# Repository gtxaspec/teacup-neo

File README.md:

# Teacup Neo

T41 (QFN96) adaptation of the [Teacup Rev-C](https://github.com/CapnRon/Teacup) T31 development board.

Targets **T41NQ (128MB)**, **T41XQ (256MB)**, and **T41LQ (64MB)** — all three are
pin-identical in the QFN96 package, so one layout serves all three as a stuffing
option (LQ needs the DDR rail set to 1.8V instead of 1.35V via the FB divider).

> **Where this is going:** teacup-neo is the single-SoC (T41) proof for a modular
> platform — a universal baseboard + per-SoC interposer modules on a **DDR4 card-edge
> socket** (UDIMM-288 desktop primary) that host any Ingenic T-series/A1 SoC
> regardless of package. Full spec in [`docs/UNIVERSAL.md`](docs/UNIVERSAL.md).

## Status

| Stage | State |
|-------|-------|
| Pin map / power design | complete, verified against 3 datasheets |
| QFN96 footprint + T41NQ symbol | KiCad-validated |
| Schematic | **netlist-verified** — all 97 SoC pins on intended nets, 0 peripheral connections lost |
| PCB netlist applied | 479 pads re-netted, 0 mismatch |
| Routing | **~83% auto-routed** (FreeRouting); 78 nets + placement + 3 shorts need GUI finishing |
| Manufacturing outputs | BOM/pos complete; Gerbers are a **draft** (board not yet fab-ready) |

**This board is NOT fab-ready.** The design (schematic + netlist) is complete and
fully verified, but the PCB was auto-routed headlessly with best-effort blind
placement. Before fabrication it needs, in the KiCad GUI:
- placement de-overlap of the bottom-side power section (7 courtyard overlaps)
- the 78 remaining ratsnest connections routed
- 3 shorts / clearance violations resolved
- **MIPI CSI routed as 100 ohm impedance-controlled differential pairs** (an
  autorouter does not do controlled impedance)
- SFC/DDR length + return-path review per the T41 Hardware Design Guide

## Power tree

2x SY8089A1AAC buck (core 0.8V/2A EN<-1.35V, DDR 1.35V EN<-1.8V) + kept AZ1117
LDOs (3.3V, 1.8V). EN cascade gives the datasheet power-on order. See `docs/POWER.md`.

## Layout

- `hw/` — KiCad project (based on TeaCup(C)3.3)
- `hw/Manufacturing/` — draft Gerbers, drill, BOM, position, DRC report
- `docs/` — pin maps, power design, netlist verification
- `scripts/` — the headless generators (footprint, symbol, schematic, PCB, routing)
- `reference/` — upstream 3.3 artifacts

Built headlessly with KiCad 9.0.2 (kicad-cli + pcbnew) + FreeRouting 1.9.0.

License: GPL-3.0 (inherited from upstream).

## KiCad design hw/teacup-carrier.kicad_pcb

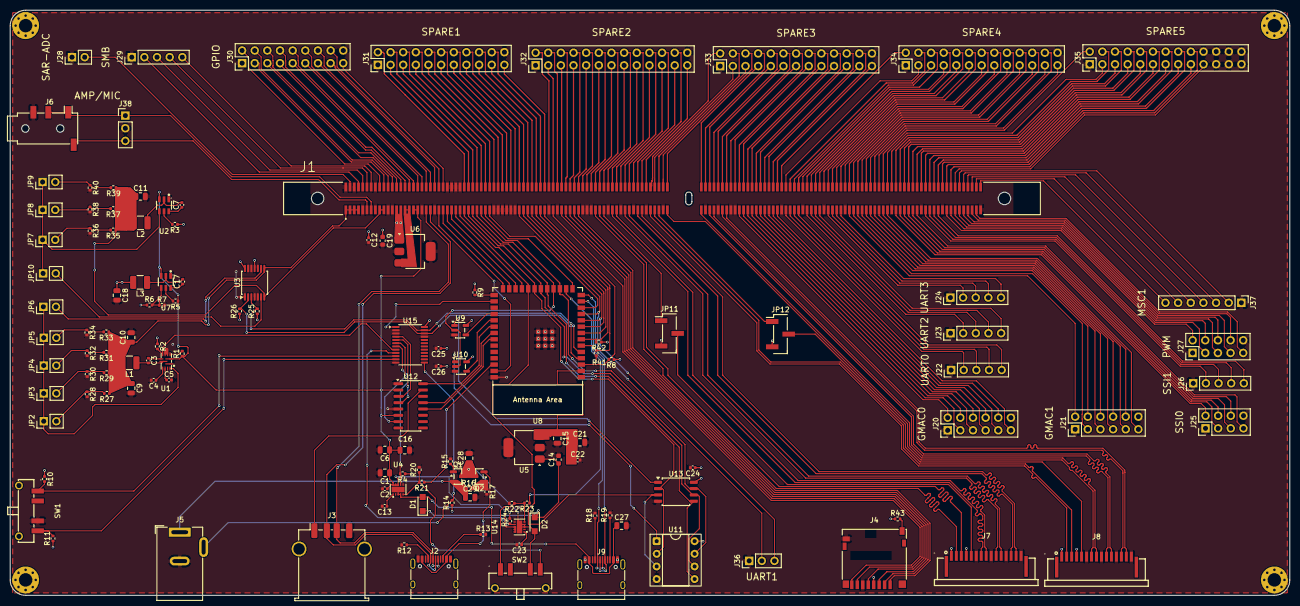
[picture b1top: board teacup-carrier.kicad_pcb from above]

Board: 4 copper layers, 257.0 x 117.5 mm, 137 parts (0 on the bottom side), 308 nets.

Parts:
C1, C9, C10, C11, C18: 22uF; C_0805_2012Metric
C2, C3, C7, C12, C17, C22, C24, C25, C26: 100nF; C_0402_1005Metric
C4: 1uF; C_0402_1005Metric
C5: 4.7nF; C_0402_1005Metric
C6, C15, C16, C21, C27, C28, C29: 10uF; C_0805_2012Metric
C13, C23: 1nF; C_0402_1005Metric
C14, C19: 1uF; C_0603_1608Metric
D1, D2: PMEG2010ER; Nexperia_CFP3_SOD-123W
H1, H2, H3, H4: MountingHole_Pad; MountingHole_2.7mm_M2.5_Pad_Via
J1: AH58893-T9B10-3F; DDR4288S0511H_UDIMM288
J2, J9: TYPE-C-31-M-12; USB_C_Receptacle_HRO_TYPE-C-31-M-12
J3: TE_292303-7; USB_A_TE_292303-7_Horizontal
J4: Hirose_DM3D-SF; microSD_HC_Hirose_DM3D-SF
J5: Wuerth_694106301002; BarrelJack_Wuerth_6941xx301002
J6: AudioJack4_Ground; Jack_3.5mm_PJ320D_Horizontal
J7, J8: SFW15R-2STE1LF; FPC-SMD_15P-P1.00_SFW15R-2STE1LF
J20: HDR_J20; PinHeader_2x06_P2.54mm_Vertical
J21: HDR_J21; PinHeader_2x06_P2.54mm_Vertical
J22: HDR_J22; PinHeader_1x05_P2.54mm_Vertical
J23: HDR_J23; PinHeader_1x05_P2.54mm_Vertical
J24: HDR_J24; PinHeader_1x05_P2.54mm_Vertical
J25: HDR_J25; PinHeader_2x04_P2.54mm_Vertical
J26: HDR_J26; PinHeader_1x05_P2.54mm_Vertical
J27: HDR_J27; PinHeader_2x05_P2.54mm_Vertical
J28: HDR_J28; PinHeader_1x02_P2.54mm_Vertical
J29: HDR_J29; PinHeader_1x05_P2.54mm_Vertical
J30: HDR_J30; PinHeader_2x09_P2.54mm_Vertical
J31: HDR_J31; PinHeader_2x11_P2.54mm_Vertical
J32: HDR_J32; PinHeader_2x13_P2.54mm_Vertical
J33: HDR_J33; PinHeader_2x13_P2.54mm_Vertical
J34: HDR_J34; PinHeader_2x13_P2.54mm_Vertical
J35: HDR_J35; PinHeader_2x13_P2.54mm_Vertical
J36: HDR_J36; PinHeader_1x03_P2.54mm_Vertical
J37: HDR_J37; PinHeader_1x07_P2.54mm_Vertical
J38: AMP_MIC_TAP; PinHeader_1x03_P2.54mm_Vertical
JP2: 0.8V; PinHeader_1x02_P2.54mm_Vertical
JP3: 0.9V; PinHeader_1x02_P2.54mm_Vertical
JP4: 1.0V; PinHeader_1x02_P2.54mm_Vertical
JP5: 1.1V; PinHeader_1x02_P2.54mm_Vertical
JP6, JP10: COMPUTER; PinHeader_1x02_P2.54mm_Vertical
JP7: 1.35V; PinHeader_1x02_P2.54mm_Vertical
JP8: 1.5V; PinHeader_1x02_P2.54mm_Vertical
JP9: 1.8V; PinHeader_1x02_P2.54mm_Vertical
JP11, JP12: EN_SEL; PinHeader_1x03_P2.54mm_Vertical_SMD_Pin1Left
L1, L2, L3: 2.2uH; L_1210_3225Metric
Q1, Q2: AO3401A; SOT-23
R1, R3, R5, R15, R17, R20, R22: 100k; R_0402_1005Metric
R2, R4, R7, R8, R9, R10, R11, R14, R24: 10k; R_0402_1005Metric
R6: 31.6k; R_0402_1005Metric
R12, R13, R18, R19: 5.1k; R_0402_1005Metric
R16, R25, R26, R41, R42: 4.7k; R_0402_1005Metric
R21, R23: 1k; R_0402_1005Metric
R27: 3.32k; R_0402_1005Metric
R28, R30, R32, R34, R36, R38, R40: 10.0k; R_0402_1005Metric
R29: 4.99k; R_0402_1005Metric
R31: 6.65k; R_0402_1005Metric
R33: 8.25k; R_0402_1005Metric
R35: 6.81k; R_0402_1005Metric
R37: 8.66k; R_0402_1005Metric
R39: 12.4k; R_0402_1005Metric
R43: 1M; R_0402_1005Metric
SW1, SW2: SSSS711403; SW-TH_SSSS711403
U1: AP62600SJ-7; QFN-12_L3.0-W2.0-P0.50-TL_AP62600SJ-7
U2, U7: AP62300WU-7; TSOT-23-6_L2.9-W1.6-P0.95-LS2.8-BL
U3: MCP4661-104E_ST; TSSOP-14_4.4x5mm_P0.65mm
U4, U14: TPS22990DMLR; WSON-10_L3.0-W2.0-P0.50-BL-EP_TI_DML
U5: AZ1117CH-3.3TRG1; SOT-223-3_TabPin2
U6: AZ1117CH-1.8TRG1; SOT-223-3_TabPin2
U8: ESP32-S3-WROOM-1-N16R2; ESP32-S3-WROOM-1
U9, U10: TS5A3166; SOT-23-5
U11: DIP-8 Socket; DIP-8_W7.62mm_Socket
U12: TPS2053BDR; SOIC-16_3.9x9.9mm_P1.27mm
U13: W25Q32JVSS; SOIC-8_5.3x5.3mm_P1.27mm
U15: TCA9555PWR; TSSOP-24_4.4x7.8mm_P0.65mm

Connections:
+1V8: J1.15, J1.16, U6.3 (OUT)
+3V3: C12.1, C18.1, C19.1, C24.1, C25.1, C26.1, J1.13, J1.14, J4.4 (VDD), J7.1, J7.4, J8.1, J8.4, JP11.3, JP12.3, L3.2, R2.1, R3.1, R4.1, R6.1, R8.1, R9.1, R10.1, R11.1, R14.1, R24.1, R25.1, R26.1, R41.1, R42.1, R43.1, U3.11 (WP), U3.14 (VDD), U6.1 (IN), U9.5 (V+), U10.5 (V+), U11.8 (VCC), U13.8 (VCC), U15.24 (VCC)
+3V3_ALWAYS: C15.1, C21.1, C22.1, U5.3 (OUT), U8.2 (3V3)
+5V_ALT: C28.1, D2.2 (A), Q1.3 (D), Q2.3 (D), SW2.3, U14.3 (VIN), U14.4 (VBIAS), U14.11 (VIN)
+5V_BMC: C27.1, D1.2 (A), J9.A4 (VBUS), J9.A9 (VBUS), J9.B4 (VBUS), J9.B9 (VBUS), U4.3 (VIN), U4.4 (VBIAS), U4.11 (VIN)
+5V_SW: C1.1, C2.1, C6.1, C16.1, J1.17, J1.18, R1.1, R5.1, U1.2 (VIN), U2.3 (VIN), U4.8 (VOUT), U4.9 (VOUT), U4.10 (VOUT), U7.3 (VIN), U12.2 (IN1), U12.6 (IN2), U14.8 (VOUT), U14.9 (VOUT), U14.10 (VOUT)
/EXP_INT: U8.28 (SPIIO6), U15.1 (~INT)
/P3V3_FB: R6.2, R7.1, U7.4 (FB)
/Q1_GATE: Q1.1 (G), R15.1
/Q2_GATE: Q2.1 (G), R16.2, R17.1
/U1_BST: C3.1, U1.7 (BST)
/U1_EN: R1.2, U1.3 (EN)
/U1_SS: C5.1, U1.10 (SS/TR)
/U1_SW: C3.2, L1.1, U1.8 (SW)
/U1_VCC: C4.1, U1.9 (VCC)
/U2_BST: C7.1, U2.6 (BST)
/U2_EN: R3.2, U2.5 (EN)
/U2_SW: C7.2, L2.1, U2.2 (SW)
/U4_CT: C13.1, U4.1 (CT)
/U5_VIN: C14.1, D1.1 (K), D2.1 (K), U5.1 (IN)
/U7_BST: C17.1, U7.6 (BST)
/U7_EN: R5.2, U7.5 (EN)
/U7_SW: C17.2, L3.1, U7.2 (SW)
/U8_BOOT: R9.2, U8.27 (GPIO0)
/U14_CT: C23.1, U14.1 (CT)
/USBC2_CC1: J9.A5 (CC1), R18.1
/USBC2_CC2: J9.B5 (CC2), R19.1
/USBC_CC1: J2.A5 (CC1), R12.1
/USBC_CC2: J2.B5 (CC2), R13.1
ALTUSB_VBUS: J2.A4 (VBUS), J2.A9 (VBUS), J2.B4 (VBUS), J2.B9 (VBUS), Q2.2 (S)
BMC_USB_DM: J9.A7 (D-), J9.B7 (D-), U8.13 (GPIO19)
BMC_USB_DP: J9.A6 (D+), J9.B6 (D+), U8.14 (GPIO20)
BOOTSEL: J1.35, U8.12 (GPIO8)
DCJACK_PRESENT: J5.3, R14.2, U15.13 (P10)
DCJACK_VBUS: C29.1, J5.1, Q1.2 (S), R16.1
EN_CS_U4: U8.30 (SPIDQS), U9.4 (IN)
EN_CS_U5: U8.31 (GPIO38), U10.4 (IN)
EN_SW_ALT: R22.1, R23.2, SW2.1, U14.5 (ON)
EN_SW_BMC: R20.1, R21.2, SW2.4, U4.5 (ON)
GMAC0_MDCK: J1.88, J20.3
GMAC0_MDIO: J1.87, J20.2
GMAC0_PHYCLK: J1.90, J20.5
GMAC0_RXD0: J1.95, J20.10
GMAC0_RXD1: J1.96, J20.11
GMAC0_RXDV: J1.94, J20.9
GMAC0_TXCLK: J1.89, J20.4
GMAC0_TXD0: J1.92, J20.7
GMAC0_TXD1: J1.93, J20.8
GMAC0_TXEN: J1.91, J20.6
GMAC1_MDCK: J1.114, J21.3
GMAC1_MDIO: J1.113, J21.2
GMAC1_PHYCLK: J1.116, J21.5
GMAC1_RXD0: J1.121, J21.10
GMAC1_RXD1: J1.122, J21.11
GMAC1_RXDV: J1.120, J21.9
GMAC1_TXCLK: J1.115, J21.4
GMAC1_TXD0: J1.118, J21.7
GMAC1_TXD1: J1.119, J21.8
GMAC1_TXEN: J1.117, J21.6
GND: C1.2, C2.2, C4.2, C5.2, C6.2, C9.2, C10.2, C11.2, C12.2, C13.2, C14.2, C15.2, C16.2, C18.2, C19.2, C21.2, C22.2, C23.2, C24.2, C25.2, C26.2, C27.2, C28.2, C29.2, J1.5, J1.8, J1.11, J1.12, J1.19, J1.22, J1.36, J1.37, J1.38, J1.39, J1.40, J1.41, J1.49, J1.51, J1.57, J1.58, J1.59, J1.63, J1.66, J1.69, J1.72, J1.76, J1.79, J1.82, J1.85, J1.86, J1.97, J1.102, J1.107, J1.112, J1.123, J1.130, J1.135, J1.144, J1.145, J1.147, J1.152, J1.169, J1.170, J1.171, J1.172, J2.A1 (GND), J2.A12 (GND), J2.B1 (GND), J2.B12 (GND), J3.4 (GND), J4.6 (VSS), J4.9 (DET_B), J5.2, J6.R2, J7.6, J7.9, J7.12, J7.15, J8.6, J8.9, J8.12, J8.15, J9.A1 (GND), J9.A12 (GND), J9.B1 (GND), J9.B12 (GND), J20.1, J20.12, J21.1, J21.12, J22.1, J23.1, J24.1, J25.1, J25.8, J26.1, J27.1, J27.10, J28.1, J29.1, J30.1, J30.18, J31.1, J31.22, J32.1, J32.26, J33.1, J33.26, J34.1, J34.26, J35.1, J35.20, J35.21, J35.22, J35.23, J35.24, J35.25, J35.26, J36.1, J37.1, J38.2, R7.2, R12.2, R13.2, R15.2, R17.2, R18.2, R19.2, R20.2, R22.2, R28.2, R30.2, R32.2, R34.2, R36.2, R38.2, R40.2, SW1.3, U1.1 (PGND), U1.4 (MODE), U1.5 (FSEL), U1.11 (GND), U2.1 (GND), U3.1 (HVC/A0), U3.4 (VSS), U3.5 (P1B), U3.10 (P0B), U3.12 (A2), U3.13 (A1), U4.6 (GND), U5.2 (GND), U6.2 (GND), U7.1 (GND), U8.1 (GND), U8.40 (GND), U8.41 (GND), U9.3 (GND), U10.3 (GND), U11.4 (GND), U12.1 (GND), U12.5 (GND), U13.4 (GND), U14.6 (GND), U15.2 (A1), U15.3 (A2), U15.12 (GND), U15.21 (A0)
GPIO0: J1.153, J30.2
GPIO1: J1.154, J30.3
GPIO2: J1.155, J30.4
GPIO3: J1.156, J30.5
GPIO4: J1.157, J30.6
GPIO5: J1.158, J30.7
GPIO6: J1.159, J30.8
GPIO7: J1.160, J30.9
GPIO8: J1.161, J30.10
GPIO9: J1.162, J30.11
GPIO10: J1.163, J30.12
GPIO11: J1.164, J30.13
GPIO12: J1.165, J30.14
GPIO13: J1.166, J30.15
GPIO14: J1.167, J30.16
GPIO15: J1.168, J30.17
HOSTED_DATA_READY: J1.24, U8.26 (GPIO45)
HOSTED_HANDSHAKE: J1.25, U8.25 (GPIO48)
HOSTED_RESET: J1.48, R8.2, U8.3 (EN)
HOSTED_SPI_CLK: J1.45, U8.8 (GPIO15)
HOSTED_SPI_CS: J1.26, U8.24 (GPIO47)
HOSTED_SPI_MISO: J1.27, U8.23 (GPIO21)
HOSTED_SPI_MOSI: J1.44, U8.9 (GPIO16)
HPOUTL: J1.7, J6.R1, J6.T, J38.1
I2C_ID_SCL: J1.46, R42.2, U8.7 (GPIO7)
I2C_ID_SDA: J1.47, R41.2, U8.6 (GPIO6)
I2C_PWR_SCL: R26.2, U3.2 (SCL), U8.5 (GPIO5), U15.22 (SCL)
I2C_PWR_SDA: R25.2, U3.3 (SDA), U8.4 (GPIO4), U15.23 (SDA)
MICLP: J1.6, J6.S, J38.3
MIPI0_CLKN: J1.65, J7.8
MIPI0_CLKP: J1.64, J7.7
MIPI0_D0N: J1.71, J7.14
MIPI0_D0P: J1.70, J7.13
MIPI0_D1N: J1.68, J7.11
MIPI0_D1P: J1.67, J7.10
MIPI0_GPIO: J1.62, JP11.1
MIPI0_SCCB_SCL: J1.61, J7.3
MIPI0_SCCB_SDA: J1.60, J7.2
MIPI0_SENSOR_EN: J7.5, JP11.2
MIPI1_CLKN: J1.78, J8.8
MIPI1_CLKP: J1.77, J8.7
MIPI1_D0N: J1.84, J8.14
MIPI1_D0P: J1.83, J8.13
MIPI1_D1N: J1.81, J8.11
MIPI1_D1P: J1.80, J8.10
MIPI1_GPIO: J1.75, JP12.1
MIPI1_SCCB_SCL: J1.74, J8.3
MIPI1_SCCB_SDA: J1.73, J8.2
MIPI1_SENSOR_EN: J8.5, JP12.2
MSC0_CD: J4.10 (DET_A), R43.2
MSC0_CLK: J1.53, J4.5 (CLK)
MSC0_CMD: J1.54, J4.3 (CMD)
MSC0_D0: J1.52, J4.7 (DAT0)
MSC0_D1: J1.50, J4.8 (DAT1)
MSC0_D2: J1.56, J4.1 (DAT2)
MSC0_D3_CD: J1.55, J4.2 (DAT3/CD)
MSC1_CLK: J1.283, J37.2
MSC1_CMD: J1.284, J37.3
MSC1_D0: J1.285, J37.4
MSC1_D1: J1.286, J37.5
MSC1_D2: J1.287, J37.6
MSC1_D3_CD: J1.288, J37.7
NOR_U4_CE: U9.1 (NO), U13.1 (~CS)
NOR_U5_CE: U10.1 (NO), U11.1 (~CS)
PG_SW5V: R4.2, U4.7 (PG), U15.7 (P03)
PG_SW5V_ALT: R24.2, U14.7 (PG), U15.9 (P05)
PG_VCORE: R2.2, U1.6 (PG), U15.8 (P04)
PWM0: J1.136, J27.2
PWM1: J1.137, J27.3
PWM2: J1.138, J27.4
PWM3: J1.139, J27.5
PWM4: J1.140, J27.6
PWM5: J1.141, J27.7
PWM6: J1.142, J27.8
PWM7: J1.143, J27.9
RESET_EN: J1.34, U8.15 (GPIO3)
SAR_AUX0: J1.146, J28.2
SFC_CLK: J1.30, U8.20 (GPIO12), U11.6 (CLK), U13.6 (CLK)
SFC_CS: J1.32, U8.18 (GPIO10), U9.2 (COM), U10.2 (COM)
SFC_IO0: J1.31, U8.19 (GPIO11), U11.5 (DI(IO0)), U13.5 (DI(IO0))
SFC_IO1: J1.29, U8.21 (GPIO13), U11.2 (DO(IO1)), U13.2 (DO(IO1))
SFC_IO2: J1.28, U8.22 (GPIO14), U11.3 (IO2), U13.3 (IO2)
SFC_IO3: J1.33, U8.17 (GPIO9), U11.7 (IO3), U13.7 (IO3)
SMB0_SCK: J1.149, J29.3
SMB0_SDA: J1.148, J29.2
SMB1_SCK: J1.151, J29.5
SMB1_SDA: J1.150, J29.4
SPARE_P173: J1.173, J31.2
SPARE_P174: J1.174, J31.3
SPARE_P175: J1.175, J31.4
SPARE_P176: J1.176, J31.5
SPARE_P177: J1.177, J31.6
SPARE_P178: J1.178, J31.7
SPARE_P179: J1.179, J31.8
SPARE_P180: J1.180, J31.9
SPARE_P181: J1.181, J31.10
SPARE_P182: J1.182, J31.11
SPARE_P183: J1.183, J31.12
SPARE_P184: J1.184, J31.13
SPARE_P185: J1.185, J31.14
SPARE_P186: J1.186, J31.15
SPARE_P187: J1.187, J31.16
SPARE_P188: J1.188, J31.17
SPARE_P189: J1.189, J31.18
SPARE_P190: J1.190, J31.19
SPARE_P191: J1.191, J31.20
SPARE_P192: J1.192, J31.21
SPARE_P193: J1.193, J32.2
SPARE_P194: J1.194, J32.3
SPARE_P195: J1.195, J32.4
SPARE_P196: J1.196, J32.5
SPARE_P197: J1.197, J32.6
SPARE_P198: J1.198, J32.7
SPARE_P199: J1.199, J32.8
SPARE_P200: J1.200, J32.9
SPARE_P201: J1.201, J32.10
SPARE_P202: J1.202, J32.11
SPARE_P203: J1.203, J32.12
SPARE_P204: J1.204, J32.13
SPARE_P205: J1.205, J32.14
SPARE_P206: J1.206, J32.15
SPARE_P207: J1.207, J32.16
SPARE_P208: J1.208, J32.17
SPARE_P209: J1.209, J32.18
SPARE_P210: J1.210, J32.19
SPARE_P211: J1.211, J32.20
SPARE_P212: J1.212, J32.21
SPARE_P213: J1.213, J32.22
SPARE_P214: J1.214, J32.23
SPARE_P215: J1.215, J32.24
SPARE_P216: J1.216, J32.25
SPARE_P217: J1.217, J33.2
SPARE_P218: J1.218, J33.3
SPARE_P219: J1.219, J33.4
SPARE_P220: J1.220, J33.5
SPARE_P221: J1.221, J33.6
SPARE_P222: J1.222, J33.7
SPARE_P223: J1.223, J33.8
SPARE_P224: J1.224, J33.9
SPARE_P225: J1.225, J33.10
SPARE_P226: J1.226, J33.11
SPARE_P227: J1.227, J33.12
SPARE_P228: J1.228, J33.13
SPARE_P229: J1.229, J33.14
SPARE_P230: J1.230, J33.15
SPARE_P231: J1.231, J33.16
SPARE_P232: J1.232, J33.17
SPARE_P233: J1.233, J33.18
SPARE_P234: J1.234, J33.19
SPARE_P235: J1.235, J33.20
SPARE_P236: J1.236, J33.21
SPARE_P237: J1.237, J33.22
SPARE_P238: J1.238, J33.23
SPARE_P239: J1.239, J33.24
SPARE_P240: J1.240, J33.25
SPARE_P241: J1.241, J34.2
SPARE_P242: J1.242, J34.3
SPARE_P243: J1.243, J34.4
SPARE_P244: J1.244, J34.5
SPARE_P245: J1.245, J34.6
SPARE_P246: J1.246, J34.7
SPARE_P247: J1.247, J34.8
SPARE_P248: J1.248, J34.9
SPARE_P249: J1.249, J34.10
SPARE_P250: J1.250, J34.11
SPARE_P251: J1.251, J34.12
SPARE_P252: J1.252, J34.13
SPARE_P253: J1.253, J34.14
SPARE_P254: J1.254, J34.15
SPARE_P255: J1.255, J34.16
SPARE_P256: J1.256, J34.17
SPARE_P257: J1.257, J34.18
SPARE_P258: J1.258, J34.19
SPARE_P259: J1.259, J34.20
SPARE_P260: J1.260, J34.21
SPARE_P261: J1.261, J34.22
SPARE_P262: J1.262, J34.23
SPARE_P263: J1.263, J34.24
SPARE_P264: J1.264, J34.25
SPARE_P265: J1.265, J35.2
SPARE_P266: J1.266, J35.3
SPARE_P267: J1.267, J35.4
SPARE_P268: J1.268, J35.5
SPARE_P269: J1.269, J35.6
SPARE_P270: J1.270, J35.7
SPARE_P271: J1.271, J35.8
SPARE_P272: J1.272, J35.9
SPARE_P273: J1.273, J35.10
SPARE_P274: J1.274, J35.11
SPARE_P275: J1.275, J35.12
SPARE_P276: J1.276, J35.13
SPARE_P277: J1.277, J35.14
SPARE_P278: J1.278, J35.15
SPARE_P279: J1.279, J35.16
SPARE_P280: J1.280, J35.17
SPARE_P281: J1.281, J35.18
SPARE_P282: J1.282, J35.19
SSI0_CE0: J1.127, J25.5
SSI0_CE1: J1.128, J25.6
SSI0_CLK: J1.124, J25.2
SSI0_DR: J1.126, J25.4
SSI0_DT: J1.125, J25.3
SSI0_GPC: J1.129, J25.7
SSI1_CE0: J1.134, J26.5
SSI1_CLK: J1.131, J26.2
SSI1_DR: J1.133, J26.4
SSI1_DT: J1.132, J26.3
SW5V_EN_ALT: R23.1, U8.16 (GPIO46)
SW5V_EN_BMC: R21.1, U8.38 (GPIO2)
SW_SENSE_1: R10.2, SW1.1, U15.10 (P06)
SW_SENSE_4: R11.2, SW1.4, U15.11 (P07)
UART0_CTS: J1.100, J22.4
UART0_RTS: J1.101, J22.5
UART0_RXD: J1.98, J22.2
UART0_TXD: J1.99, J22.3
UART1_RX: J1.42, J36.2, U8.11 (GPIO18)
UART1_TX: J1.43, J36.3, U8.10 (GPIO17)
UART2_CTS: J1.105, J23.4
UART2_RTS: J1.106, J23.5
UART2_RXD: J1.103, J23.2
UART2_TXD: J1.104, J23.3
UART3_CTS: J1.110, J24.4
UART3_RTS: J1.111, J24.5
UART3_RXD: J1.108, J24.2
UART3_TXD: J1.109, J24.3
USB1_VBUS_OUT: J3.1 (VBUS), U12.15 (OUT1)
USBA_HOST_DM: J1.21, J2.A7 (D-), J2.B7 (D-), J3.2 (D-)
USBA_HOST_DP: J1.20, J2.A6 (D+), J2.B6 (D+), J3.3 (D+)
USB_EN1: U12.3 (EN1), U15.4 (P00)
USB_EN2: U12.4 (EN2), U15.5 (P01)
USB_EN3: U12.7 (EN3), U15.6 (P02)
USB_OC1: U8.32 (MTCK), U12.16 (OC1)
USB_OC2: U8.33 (MTDO), U12.13 (OC2)
USB_OC3: U8.34 (MTDI), U12.12 (OC3)
VCORE: C9.1, C10.1, J1.1, J1.2, J1.3, J1.4, L1.2, R27.1, R29.1, R31.1, R33.1, U3.8 (P0A)
VCORE_FB_0V8: JP2.2, R27.2, R28.1
VCORE_FB_0V9: JP3.2, R29.2, R30.1
VCORE_FB_1V0: JP4.2, R31.2, R32.1
VCORE_FB_1V1: JP5.2, R33.2, R34.1
VCORE_FB_DIGIPOT: JP6.2, U3.9 (P0W)
VCORE_FB_SEL: JP2.1, JP3.1, JP4.1, JP5.1, JP6.1, U1.12 (FB)
VCORE_SNS: J1.23, U8.39 (GPIO1)
VDDR: C11.1, J1.9, J1.10, L2.2, R35.1, R37.1, R39.1, U3.7 (P1A)
VDDR_FB_1V5: JP8.2, R37.2, R38.1
VDDR_FB_1V8: JP9.2, R39.2, R40.1
VDDR_FB_1V35: JP7.2, R35.2, R36.1
VDDR_FB_DIGIPOT: JP10.2, U3.6 (P1W)
VDDR_FB_SEL: JP7.1, JP8.1, JP9.1, JP10.1, U2.4 (FB)

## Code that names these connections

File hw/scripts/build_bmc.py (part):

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    12: "BOOTSEL",
    13: "BMC_USB_DM", 14: "BMC_USB_DP",   # now via dedicated J9, not J2
    15: "RESET_EN",
    16: "SW5V_EN_ALT",               # GPIO select: alt-branch load switch (U14) -- native, margin testing
    17: "SFC_IO3", 18: "SFC_CS", 19: "SFC_IO0",
    20: "SFC_CLK", 21: "SFC_IO1", 22: "SFC_IO2",
    23: "HOSTED_SPI_MISO", 24: "HOSTED_SPI_CS",    # ESP-Hosted full-duplex SPI to interposer
    25: "HOSTED_HANDSHAKE",          # ESP-Hosted: co-processor -> host, data-ready-to-send
    26: "HOSTED_DATA_READY",         # ESP-Hosted: co-processor -> host, packet pending
    27: "U8_BOOT",                  # GPIO0/BOOT strap, R9 pull-up
    28: "EXP_INT",                   # U15 (TCA9555) interrupt, active low
    29: None, 35: None,              # spare
    30: "EN_CS_U4", 31: "EN_CS_U5",  # native, margin testing
    32: "USB_OC1", 33: "USB_OC2", 34: "USB_OC3",   # native -- fast overcurrent response
    36: "ESP32_CONSOLE_RX", 37: "ESP32_CONSOLE_TX",
    38: "SW5V_EN_BMC", 39: "VCORE_SNS",   # GPIO select: BMC-branch load switch (U4) -- native, margin testing
}
for num, spec in U8_PINS.items():
    ic_pin(U8, u8x, u8y, num, spec)
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    s.place(TS, ref, "TS5A3166", tx, y, 0, footprint="Package_TO_SOT_SMD:SOT-23-5",
            ref_at=(tx, y - S(6), 0), value_at=(tx, y + S(6), 0))
    ic_pin(TS, tx, y, 1, no_net)      # NO
    ic_pin(TS, tx, y, 2, "SFC_CS")    # COM
    ic_pin(TS, tx, y, 3, GNDF)        # GND
    ic_pin(TS, tx, y, 4, in_net)      # IN
    ic_pin(TS, tx, y, 5, P3V3F)       # V+
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s.place(SW, "SW1", "SSSS711403", swx, swy, 0,
        footprint="teacup-carrier:SW-TH_SSSS711403",
        ref_at=(swx, swy + S(4), 0), value_at=(swx, swy + S(6), 0))
ic_pin(SW, swx, swy, 1, "SW_SENSE_1")
ic_pin(SW, swx, swy, 3, GNDF)
ic_pin(SW, swx, swy, 4, "SW_SENSE_4")
# pins 2/5/6 deliberately NC per the confirmed datasheet pinout

vert2("Device:R", "R10", "10k", S(160), S(104), P3V3F, "SW_SENSE_1", "Resistor_SMD:R_0402_1005Metric")
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s.place(SW2, "SW2", "SSSS711403", sw2x, sw2y, 0,
        footprint="teacup-carrier:SW-TH_SSSS711403",
        ref_at=(sw2x, sw2y + S(4), 0), value_at=(sw2x, sw2y + S(6), 0))
ic_pin(SW2, sw2x, sw2y, 1, "EN_SW_ALT")
ic_pin(SW2, sw2x, sw2y, 3, "+5V_ALT")
ic_pin(SW2, sw2x, sw2y, 4, "EN_SW_BMC")
# pins 2/5/6 deliberately NC per the confirmed datasheet pinout

# ============ Primary NOR flash (U13, soldered SOIC-8 W25Q32JVSS) ============
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s.place(SOIC_NOR, "U13", "W25Q32JVSS", n4x, n4y, 0,
        footprint="Package_SO:SOIC-8_5.3x5.3mm_P1.27mm",
        ref_at=(n4x - S(10), n4y - S(10), 0), value_at=(n4x - S(10), n4y - S(8), 0))
ic_pin(SOIC_NOR, n4x, n4y, 1, "NOR_U4_CE")  # ~CS
ic_pin(SOIC_NOR, n4x, n4y, 2, "SFC_IO1")    # DO
ic_pin(SOIC_NOR, n4x, n4y, 3, "SFC_IO2")    # IO2
ic_pin(SOIC_NOR, n4x, n4y, 4, GNDF)         # GND (bottom)
ic_pin(SOIC_NOR, n4x, n4y, 5, "SFC_IO0")    # DI
ic_pin(SOIC_NOR, n4x, n4y, 6, "SFC_CLK")    # CLK
ic_pin(SOIC_NOR, n4x, n4y, 7, "SFC_IO3")    # IO3
ic_pin(SOIC_NOR, n4x, n4y, 8, P3V3F)        # VCC (top)
vert2("Device:C", "C24", "100nF", n4x + S(22), n4y, P3V3F, GNDF, "Capacitor_SMD:C_0402_1005Metric")

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s.place(DIP, "U11", "DIP-8 Socket", dx, dy, 0,
        footprint="Package_DIP:DIP-8_W7.62mm_Socket",
        ref_at=(dx - S(10), dy - S(10), 0), value_at=(dx - S(10), dy - S(8), 0))
ic_pin(DIP, dx, dy, 1, "NOR_U5_CE")   # ~CS
ic_pin(DIP, dx, dy, 2, "SFC_IO1")     # DO
ic_pin(DIP, dx, dy, 3, "SFC_IO2")     # IO2
ic_pin(DIP, dx, dy, 4, GNDF)          # GND (bottom)
ic_pin(DIP, dx, dy, 5, "SFC_IO0")     # DI
ic_pin(DIP, dx, dy, 6, "SFC_CLK")     # CLK
ic_pin(DIP, dx, dy, 7, "SFC_IO3")     # IO3
ic_pin(DIP, dx, dy, 8, P3V3F)         # VCC (top)
vert2("Device:C", "C25", "100nF", dx + S(22), dy, P3V3F, GNDF, "Capacitor_SMD:C_0402_1005Metric")

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    ic_pin(TPS, tx, ty, num, spec)

# ============ GPIO expander (U15, TCA9555PWR) ============
# Frees 9 native ESP32 GPIOs (USB_EN1-3, PG_SW5V/VCORE/SW5V_ALT, SW_SENSE_1/4,
# DCJACK_PRESENT) for the ESP-Hosted SPI link -- all slow status/enable
# signals with no real timing requirement, unlike flash chip-select and the
# power-domain switching GPIOs, which stay native for margin testing.
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s.place(EXP, "U15", "TCA9555PWR", ex, ey, 0,
        footprint="Package_SO:TSSOP-24_4.4x7.8mm_P0.65mm",
        ref_at=(ex - S(16), ey - S(24), 0), value_at=(ex - S(16), ey - S(22), 0))
ic_pin(EXP, ex, ey, 1, "EXP_INT")
ic_pin(EXP, ex, ey, 2, GNDF)     # A1
ic_pin(EXP, ex, ey, 3, GNDF)     # A2
ic_pin(EXP, ex, ey, 4, "USB_EN1")
ic_pin(EXP, ex, ey, 5, "USB_EN2")
ic_pin(EXP, ex, ey, 6, "USB_EN3")
ic_pin(EXP, ex, ey, 7, "PG_SW5V")
ic_pin(EXP, ex, ey, 8, "PG_VCORE")
ic_pin(EXP, ex, ey, 9, "PG_SW5V_ALT")
ic_pin(EXP, ex, ey, 10, "SW_SENSE_1")
ic_pin(EXP, ex, ey, 11, "SW_SENSE_4")
ic_pin(EXP, ex, ey, 12, GNDF)
ic_pin(EXP, ex, ey, 13, "DCJACK_PRESENT")
# pins 14-20 (P11-P17) deliberately NC -- spare I/O for future use
ic_pin(EXP, ex, ey, 21, GNDF)    # A0
ic_pin(EXP, ex, ey, 22, "I2C_PWR_SCL")
ic_pin(EXP, ex, ey, 23, "I2C_PWR_SDA")
ic_pin(EXP, ex, ey, 24, P3V3F)
vert2("Device:C", "C26", "100nF", ex, ey + S(35), P3V3F, GNDF, "Capacitor_SMD:C_0402_1005Metric")

# I2C_ID bus pull-ups (crosses J1 to whichever interposer's own EEPROM is
# seated, SS7 -- master on ESP32 GPIO6/7). Live on the carrier, not the
# interposer, because the carrier side is always populated regardless of
# which (or whether any) interposer is plugged in. 4.7k to +3V3.
vert2("Device:R", "R41", "4.7k", S(166), S(20), P3V3F, "I2C_ID_SDA", "Resistor_SMD:R_0402_1005Metric")
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
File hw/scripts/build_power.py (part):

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
s.flag("GND", P1(1), "P", "left")            # PGND
pin_net(P1(2), "+5V_SW", "left")             # VIN
pin_net(P1(3), "U1_EN", "left")              # EN
s.flag("GND", P1(4), "P", "left")            # MODE
s.flag("GND", P1(5), "P", "left")            # FSEL
pin_net(P1(6), "PG_VCORE", "left")           # PG (open-drain, R2 pulls up)
pin_net(P1(12), "VCORE_FB_SEL", "right")     # FB -- jumper common pole, see JP2-JP6 below
s.flag("GND", P1(11), "P", "right")          # GND
pin_net(P1(10), "U1_SS", "right")            # SS/TR
pin_net(P1(9), "U1_VCC", "right")            # VCC
pin_net(P1(8), "U1_SW", "right")             # SW
pin_net(P1(7), "U1_BST", "right")            # BST

# U1 passive islands
py1 = S(48)
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P2 = lambda n: s.pin(U2, u2x, u2y, 0, str(n))

s.flag("GND", P2(1), "P", "left")            # GND
pin_net(P2(2), "U2_SW", "left")              # SW
pin_net(P2(3), "+5V_SW", "left")             # VIN
pin_net(P2(4), "VDDR_FB_SEL", "right")       # FB -- jumper common pole, see JP7-JP10 below
pin_net(P2(5), "U2_EN", "right")             # EN
pin_net(P2(6), "U2_BST", "right")            # BST

py2 = S(84)
vert2("Device:C", "C6", "10uF", S(20), py2, "+5V_SW", GNDF, "Capacitor_SMD:C_0805_2012Metric")
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P7 = lambda n: s.pin(U2, u7x, u7y, 0, str(n))

s.flag("GND", P7(1), "P", "left")            # GND
pin_net(P7(2), "U7_SW", "left")              # SW
pin_net(P7(3), "+5V_SW", "left")             # VIN
pin_net(P7(4), "P3V3_FB", "right")           # FB
pin_net(P7(5), "U7_EN", "right")             # EN
pin_net(P7(6), "U7_BST", "right")            # BST

py7 = S(120)
vert2("Device:C", "C16", "10uF", S(20), py7, "+5V_SW", GNDF, "Capacitor_SMD:C_0805_2012Metric")
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s.place(DSCH, "D1", "PMEG2010ER", d1x, d1y, 0,
        footprint="Diode_SMD:Nexperia_CFP3_SOD-123W",
        ref_at=(d1x, d1y - S(3), 0), value_at=(d1x, d1y + S(3), 0))
pin_net(s.pin(DSCH, d1x, d1y, 0, "1"), "U5_VIN", "left")     # K
pin_net(s.pin(DSCH, d1x, d1y, 0, "2"), "+5V_BMC", "right")   # A

d2x, d2y = S(108), S(22)
s.place(DSCH, "D2", "PMEG2010ER", d2x, d2y, 0,
        footprint="Diode_SMD:Nexperia_CFP3_SOD-123W",
        ref_at=(d2x, d2y - S(3), 0), value_at=(d2x, d2y + S(3), 0))
pin_net(s.pin(DSCH, d2x, d2y, 0, "1"), "U5_VIN", "left")     # K
pin_net(s.pin(DSCH, d2x, d2y, 0, "2"), "+5V_ALT", "right")   # A

# ============ Always-on 3.3V LDO (U5, AZ1117CH-3.3) ============
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        footprint="Package_TO_SOT_SMD:SOT-223-3_TabPin2",
        extra_props={"Datasheet": "https://lcsc.com/product-detail/C92102.html"},
        ref_at=(u5x, u5y - S(6), 0), value_at=(u5x, u5y - S(4), 0))
pin_net(s.pin(REG, u5x, u5y, 0, "1"), "U5_VIN", "left")
s.flag("GND", s.pin(REG, u5x, u5y, 0, "2"), "P", "down")
pin_net(s.pin(REG, u5x, u5y, 0, "3"), "+3V3_ALWAYS", "right")
vert2("Device:C", "C14", "1uF", S(128), S(16), "U5_VIN", GNDF, "Capacitor_SMD:C_0603_1608Metric")
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# ============ BMC-branch load switch (U4, TPS22990DMLR) ============
# Gates +5V_BMC (the ESP32's own dedicated USB-C, isolated from every
# other source) onto the shared +5V_SW rail. EN_SW_BMC is arbitrated
# between GPIO (SW5V_EN_BMC, through R21), its own pulldown (R20), and
# SW2's throw1 on the bmc sheet (crosses in via this same label) -- one
# throw of the same on-off-on switch that forces the ALT branch (U14) on
# the other throw.
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        ref_at=(u4x, u4y - S(9), 0), value_at=(u4x, u4y + S(9), 0))
P4 = lambda n: s.pin(U4, u4x, u4y, 0, str(n))

pin_net(P4(1), "U4_CT", "left")              # CT
# pin 2 NC -- deliberately unconnected per datasheet
pin_net(P4(3), "+5V_BMC", "left")            # VIN
pin_net(P4(4), "+5V_BMC", "left")            # VBIAS (tied to VIN)
pin_net(P4(5), "EN_SW_BMC", "left")          # ON
s.flag("GND", P4(6), "P", "right")           # GND
pin_net(P4(7), "PG_SW5V", "right")           # PG (open-drain, R4 pulls up)
pin_net(P4(8), "+5V_SW", "right")            # VOUT
pin_net(P4(9), "+5V_SW", "right")            # VOUT
pin_net(P4(10), "+5V_SW", "right")           # VOUT
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# ============ ALT-branch load switch (U14, TPS22990DMLR) ============
# Gates +5V_ALT (the priority-OR'd DC jack / alt USB-C, see io.kicad_sch
# Q1/Q2) onto the same shared +5V_SW rail. EN_SW_ALT is arbitrated the
# same way as EN_SW_BMC (GPIO + pulldown) but is ALSO hard-overridable by
# SW2's throw4 on the bmc sheet, which ties this node to +5V_ALT (SW2's
# pole) when selected -- low-impedance, beats GPIO16's resistor-limited
# drive. Center = neither throw engaged, GPIO has full control.
U14 = "teacup-carrier:TPS22990DMLR"
u14x, u14y = S(210), S(76)
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        ref_at=(u14x, u14y - S(9), 0), value_at=(u14x, u14y + S(9), 0))
P14 = lambda n: s.pin(U14, u14x, u14y, 0, str(n))

pin_net(P14(1), "U14_CT", "left")            # CT
# pin 2 NC -- deliberately unconnected per datasheet
pin_net(P14(3), "+5V_ALT", "left")           # VIN
pin_net(P14(4), "+5V_ALT", "left")           # VBIAS (tied to VIN)
pin_net(P14(5), "EN_SW_ALT", "left")         # ON
s.flag("GND", P14(6), "P", "right")          # GND
pin_net(P14(7), "PG_SW5V_ALT", "right")      # PG (open-drain, R24 pulls up)
pin_net(P14(8), "+5V_SW", "right")           # VOUT (same shared rail as U4)
pin_net(P14(9), "+5V_SW", "right")           # VOUT
pin_net(P14(10), "+5V_SW", "right")          # VOUT
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vert2("Device:R", "R24", "10k", S(210), S(96), P3V3F, "PG_SW5V_ALT", "Resistor_SMD:R_0402_1005Metric")

# ALT-branch EN arbitration -- same topology as the BMC branch, plus SW2's
# hard override on the bmc sheet (crosses in via the EN_SW_ALT label).
vert2("Device:R", "R23", "1k", S(192), S(60), "SW5V_EN_ALT", "EN_SW_ALT", "Resistor_SMD:R_0402_1005Metric")
vert2("Device:R", "R22", "100k", S(201), S(60), "EN_SW_ALT", GNDF, "Resistor_SMD:R_0402_1005Metric")

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P3 = lambda n: s.pin(U3, u3x, u3y, 0, str(n))

s.flag("GND", P3(1), "P", "left")            # HVC/A0
pin_net(P3(2), "I2C_PWR_SCL", "left")        # SCL
pin_net(P3(3), "I2C_PWR_SDA", "left")        # SDA
s.flag("GND", P3(4), "P", "left")            # VSS
s.flag("GND", P3(5), "P", "left")            # P1B
pin_net(P3(6), "VDDR_FB_DIGIPOT", "left")    # P1W -- one jumper throw, not hard-wired to FB anymore
pin_net(P3(7), "VDDR", "left")               # P1A
pin_net(P3(8), "VCORE", "right")             # P0A
pin_net(P3(9), "VCORE_FB_DIGIPOT", "right")  # P0W -- one jumper throw, not hard-wired to FB anymore
s.flag("GND", P3(10), "P", "right")          # P0B
s.flag("+3V3", P3(11), "P", "right")         # WP
s.flag("GND", P3(12), "P", "right")          # A2
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vert2("Device:C", "C12", "100nF", S(200), S(130), P3V3F, GNDF, "Capacitor_SMD:C_0402_1005Metric")

# I2C_PWR bus pull-ups (digipot U3 + GPIO expander U15 on the bmc sheet,
# master on ESP32 GPIO4/5) -- neither device supplies its own, and I2C is
# open-drain, so without these the bus simply doesn't work. 4.7k to +3V3,
# standard value for a short, low-device-count, carrier-local bus.
vert2("Device:R", "R25", "4.7k", S(209), S(130), P3V3F, "I2C_PWR_SDA", "Resistor_SMD:R_0402_1005Metric")
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# ============ VCORE/VDDR voltage-select jumpers ============
# Explicit user direction: replace "trust the digipot's NV memory" as the
# power-up safety story with a hardware-deterministic default. U1/U2's FB
# pins (VCORE_FB_SEL / VDDR_FB_SEL above) are now the common pole of a
# jumper bank, not hard-wired to the digipot wiper. Every candidate divider
# -- 4 fixed presets for VCORE, 3 for VDDR, plus the digipot itself as one
# more candidate -- stays permanently powered across VOUT/GND regardless of
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def jumper(ref, val, x, y, pole_net, throw_net):
    # Ref/value pushed above/below the pin span (matching the headers
    # sheet's proven convention) rather than vert2's default beside-the-body
    # offset -- the pole/throw net labels here (VCORE_FB_SEL etc.) are long
    # enough to run into a close-beside ref/value at this tight jumper
    # pitch. Confirmed via check_overlaps.py.
    s.place(JHDR, ref, val, x, y, 0, footprint=JFP,
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
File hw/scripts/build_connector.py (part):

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    # to arrive at the FFC, so they can be routed straight across without
    # having to cross over each other (which is what forces vias). Per
    # explicit user direction, 2026-07-13.
    60: "MIPI0_GPIO", 61: "MIPI0_SCCB_SDA", 62: "MIPI0_SCCB_SCL",
    63: "GND", 64: "MIPI0_CLKP", 65: "MIPI0_CLKN",
    66: "GND", 67: "MIPI0_D1P", 68: "MIPI0_D1N",
    69: "GND", 70: "MIPI0_D0P", 71: "MIPI0_D0N",
    72: "GND",
    # MIPI1: same pattern, same reasoning (matches J8's FFC pin order).
    73: "MIPI1_GPIO", 74: "MIPI1_SCCB_SDA", 75: "MIPI1_SCCB_SCL",
    76: "GND", 77: "MIPI1_CLKP", 78: "MIPI1_CLKN",
    79: "GND", 80: "MIPI1_D1P", 81: "MIPI1_D1N",
    82: "GND", 83: "MIPI1_D0P", 84: "MIPI1_D0N",
    85: "GND",
}
# ESP-Hosted's host-driven reset line -- ties straight to the BMC ESP32-S3's
# own EN/RST pin (HOSTED_RESET on the bmc sheet), not a GPIO. Host side must
# drive it open-drain (only pulls low) so it doesn't fight R8's pull-up.
UNIT2[86] = "HOSTED_RESET"
# 87-96: primary GMAC (RGMII, T-series MAC position -- T31/T40 reduced
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    unit_pin(u3x, u3y, 3, num, spec)

# ============ Unit 4 (pins 145-192): SAR-ADC + general SMB/I2C + plain GPIO ============
# SAR_AUX0 matches the T41 reference board's dedicated ADC_AUX0 pin (old/docs/
# t31zx_teacup_pinuse.csv pin 32) -- a single-channel analog input outside the
# GPIO mux tables on every SoC checked, not a multi-channel SADC. SMB0/SMB1 here
# are the carrier's GENERAL system I2C headers -- kept electrically separate
# from I2C_ID_SDA/SCL (unit 1, pins 23/24, the carrier-ID EEPROM bus), same
# isolation principle already used for VGA/HDMI DDC on the A1 interposer (SS10).
# GPIO0-15 are plain unclaimed superset pins for whatever's left after every
# named peripheral above -- deliberately generic, not tied to a specific SoC
# pin identity, since "remaining plain GPIO" is itself one of the user's
# approved header clusters. Pins 170-192 (23 pins), plus all of units 5-6
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    UNIT4[153 + i] = f"GPIO{i}"
UNIT4[169] = "GND"
# P170-171 claimed for the audio pair (HPOUTL relocated down from unit 2's
# old pin 58, MICLP for J6's mic signal per TeaCup(C)3.3's J10) -- geography
# -first (UNIVERSAL.md SS8: "audio by the codec block"), clustered together
# rather than HPOUTL sitting alone far from MICLP. GND on both sides (169,
# 172) preserves the same "sensitive analog, isolated on both sides" intent
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
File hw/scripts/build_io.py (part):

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s.place(AO3401A, "Q1", "AO3401A", q1x, q1y, 0,
        footprint="Package_TO_SOT_SMD:SOT-23",
        ref_at=(q1x - S(8), q1y - S(3), 0), value_at=(q1x - S(8), q1y + S(3), 0))
q_pin(AO3401A, q1x, q1y, AO_S, "DCJACK_VBUS")
q_pin(AO3401A, q1x, q1y, AO_D, "+5V_ALT")
q_pin(AO3401A, q1x, q1y, AO_G, "Q1_GATE")
vert2("Device:R", "R15", "100k", q1x, S(145), "Q1_GATE", GNDF, "Resistor_SMD:R_0402_1005Metric")

q2x, q2y = S(105), S(130)
s.place(AO3401A, "Q2", "AO3401A", q2x, q2y, 0,
        footprint="Package_TO_SOT_SMD:SOT-23",
        ref_at=(q2x - S(8), q2y - S(3), 0), value_at=(q2x - S(8), q2y + S(3), 0))
q_pin(AO3401A, q2x, q2y, AO_S, "ALTUSB_VBUS")
q_pin(AO3401A, q2x, q2y, AO_D, "+5V_ALT")
q_pin(AO3401A, q2x, q2y, AO_G, "Q2_GATE")
vert2("Device:R", "R16", "4.7k", S(105), S(145), "DCJACK_VBUS", "Q2_GATE", "Resistor_SMD:R_0402_1005Metric")
vert2("Device:R", "R17", "100k", S(114), S(145), "Q2_GATE", GNDF, "Resistor_SMD:R_0402_1005Metric")
# Bulk/bypass cap at the OR'd output node, before +5V_ALT reaches U14
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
